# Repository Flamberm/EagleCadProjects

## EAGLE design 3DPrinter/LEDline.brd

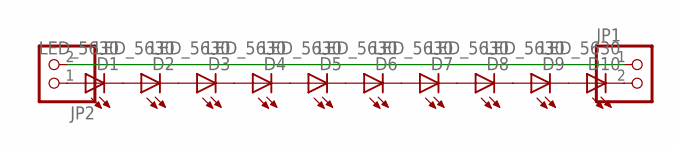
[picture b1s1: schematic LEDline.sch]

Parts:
D1, D2, D3, D4, D5, D6, D7, D8, D9, D10: LED_5630; LED5730
JP1, JP2: PINHD-1X2/90; 1X02/90

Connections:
unnamed: D1.C, D2.A, D2.A1 (A)
unnamed: D2.C, D3.A, D3.A1 (A)
unnamed: D3.C, D4.A, D4.A1 (A)
unnamed: D4.C, D5.A, D5.A1 (A)
unnamed: D5.C, D6.A, D6.A1 (A)
unnamed: D6.C, D7.A, D7.A1 (A)
unnamed: D7.C, D8.A, D8.A1 (A)
unnamed: D8.C, D9.A, D9.A1 (A)
unnamed: D9.C, D10.A, D10.A1 (A)
unnamed: D10.C, JP1.2
unnamed: D1.A, D1.A1 (A), JP2.1
unnamed: JP1.1, JP2.2

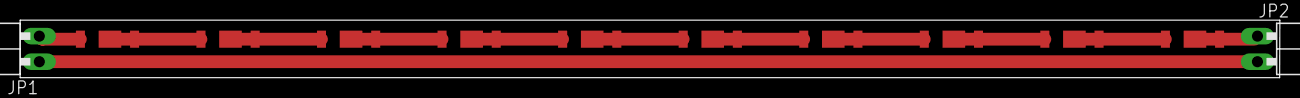
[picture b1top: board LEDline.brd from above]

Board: 2 copper layers, 125.1 x 5.7 mm, 12 parts (0 on the bottom side), 12 nets.

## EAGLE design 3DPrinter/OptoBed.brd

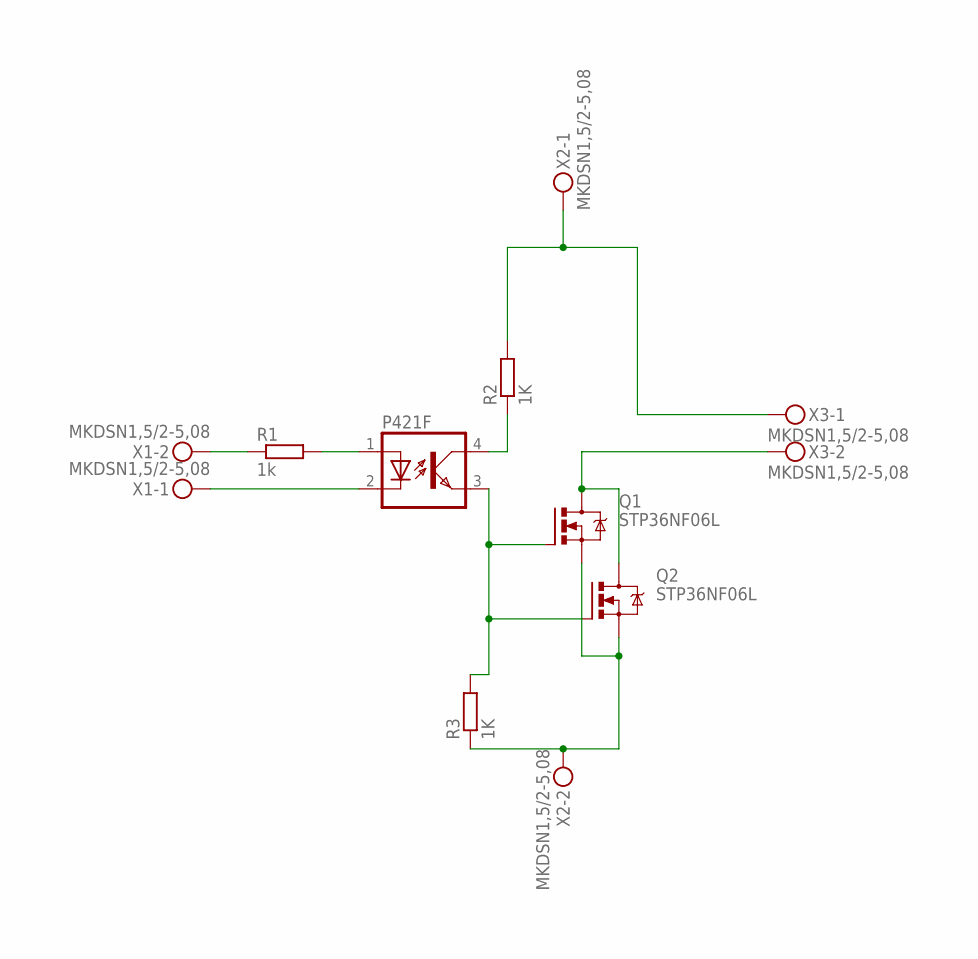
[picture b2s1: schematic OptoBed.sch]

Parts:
P421F: OPTOTRANSPC817; DIL04
Q1, Q2: STP36NF06L; TO220BV
R1: 1k; R0805
R2, R3: 1K; R0805
X1, X2, X3: MKDSN1,5/2-5,08

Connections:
unnamed: R1.1, X1.2
unnamed: P421F.1 (A), R1.2
unnamed: P421F.2 (C), X1.1
unnamed: P421F.3 (EMIT), Q1.G, Q2.G, R3.2
unnamed: Q1.S, Q2.S, R3.1, X2.2
unnamed: Q1.D, Q2.D, X3.2
unnamed: P421F.4 (COL), R2.1
unnamed: R2.2, X2.1, X3.1

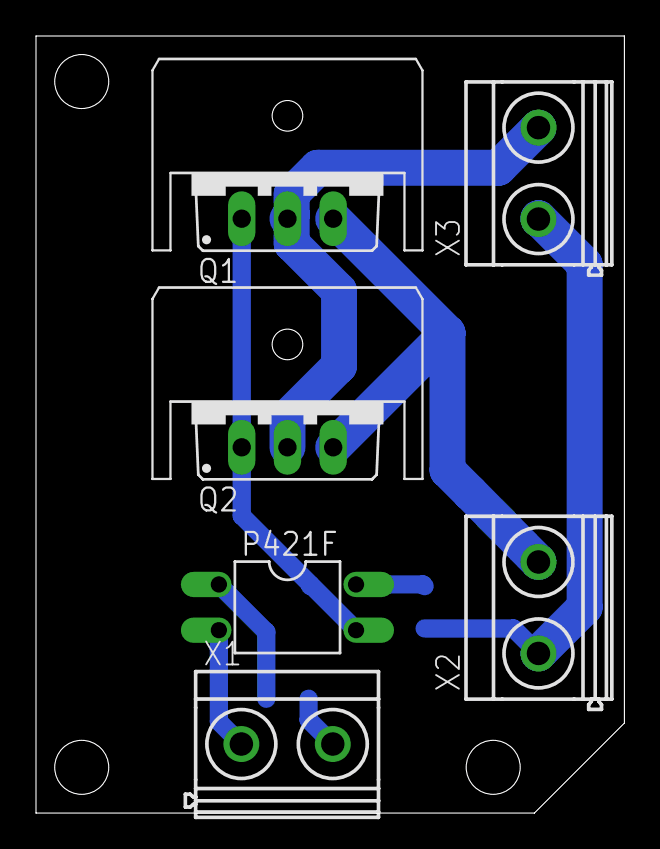
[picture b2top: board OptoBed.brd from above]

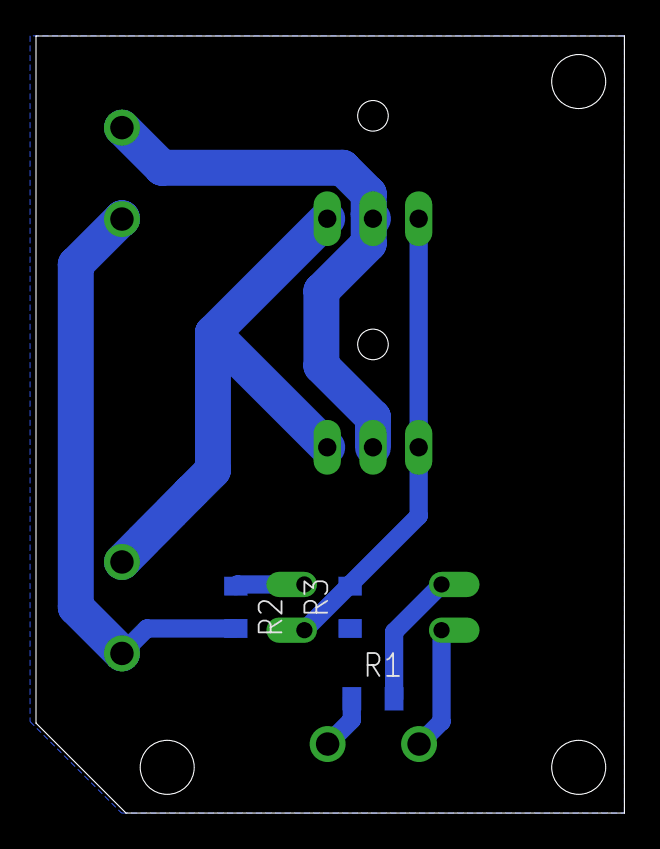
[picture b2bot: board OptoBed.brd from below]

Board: 2 copper layers, 32.7 x 43.2 mm, 11 parts (3 on the bottom side), 8 nets.

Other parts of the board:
U$1, U$2: SK95-3M3_HOLE

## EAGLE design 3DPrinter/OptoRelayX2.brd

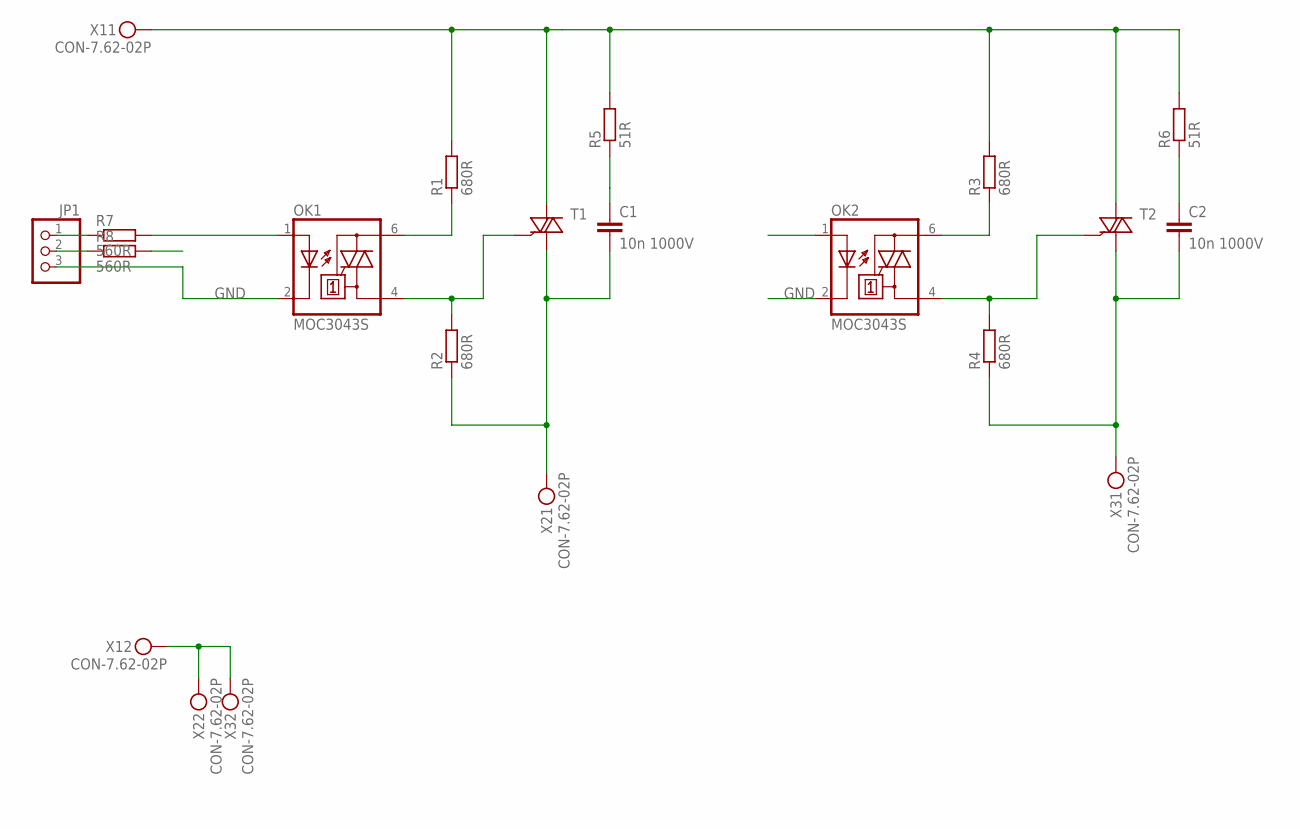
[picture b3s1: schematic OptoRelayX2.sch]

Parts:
C1, C2: 10n 1000V; C050-024X044
JP1: PINHD-1X3; 1X03
OK1, OK2: MOC3043S; DIL6-SMD
R1, R2, R3, R4: 680R; MF-05
R5, R6: 51R; MF-2
R7, R8: 560R; R0805
T1, T2: TRIAC; DPAK
X1, X2, X3: CON-7.62-02P; KF25C-7.62-02P-13

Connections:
GND: JP1.3, OK1.2 (C), OK2.2 (C)
unnamed: X1.P$2, X2.P$2, X3.P$2
unnamed: R1.2, R3.2, R5.2, R6.2, T1.D (A2), T2.D (A2), X1.P$1
unnamed: C1.1, R5.1
unnamed: OK1.6 (A2), R1.1
unnamed: OK2.6 (A2), R3.1
unnamed: OK2.4 (A1), R4.2, T2.S (G)
unnamed: OK1.4 (A1), R2.2, T1.S (G)
unnamed: C1.2, R2.1, T1.G (A1), X2.P$1
unnamed: C2.2, R4.1, T2.G (A1), X3.P$1
unnamed: C2.1, R6.1
unnamed: JP1.1, R7.1
unnamed: JP1.2, R8.1
unnamed: OK1.1 (A), R7.2
unnamed: OK2.1 (A), R8.2

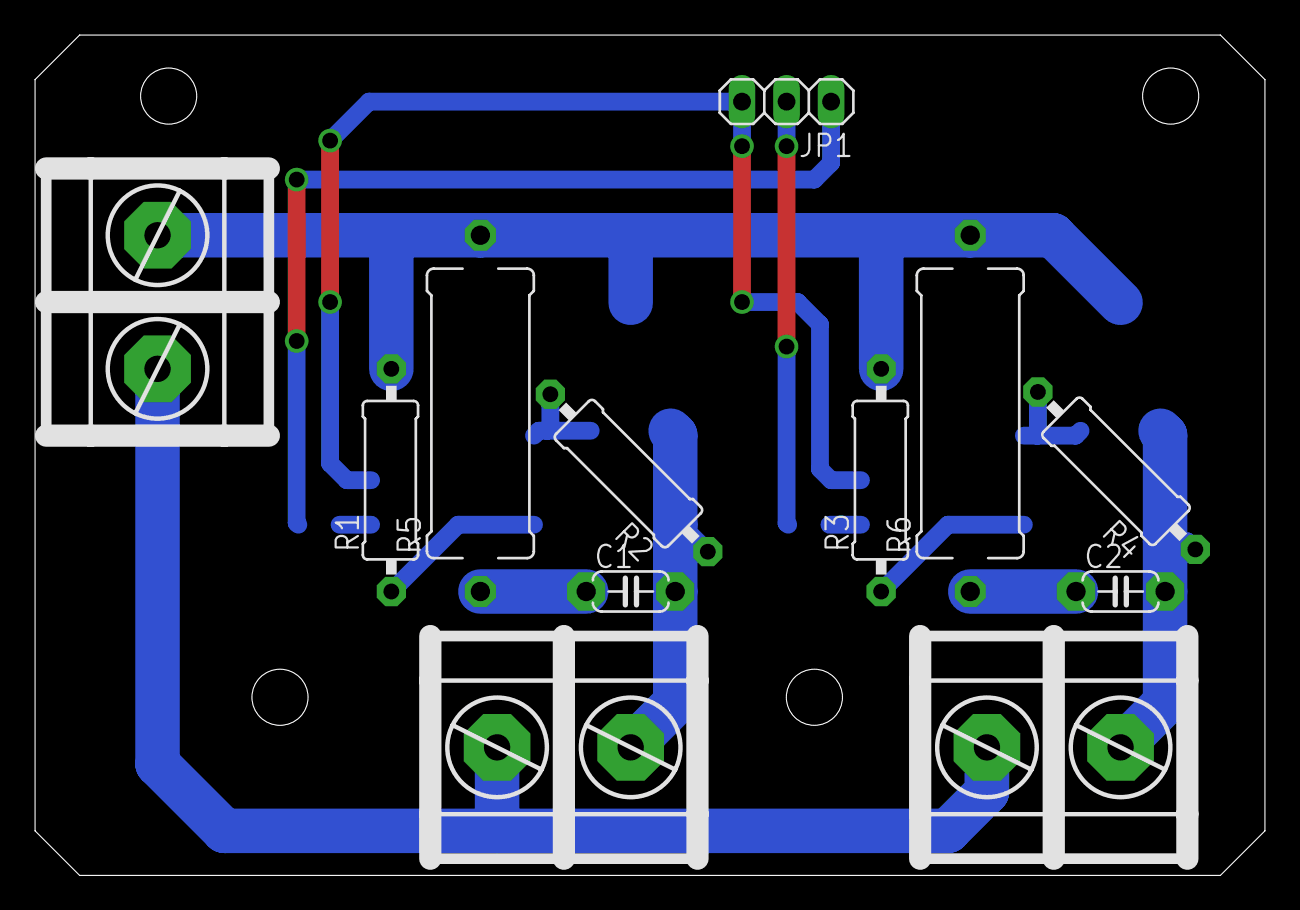
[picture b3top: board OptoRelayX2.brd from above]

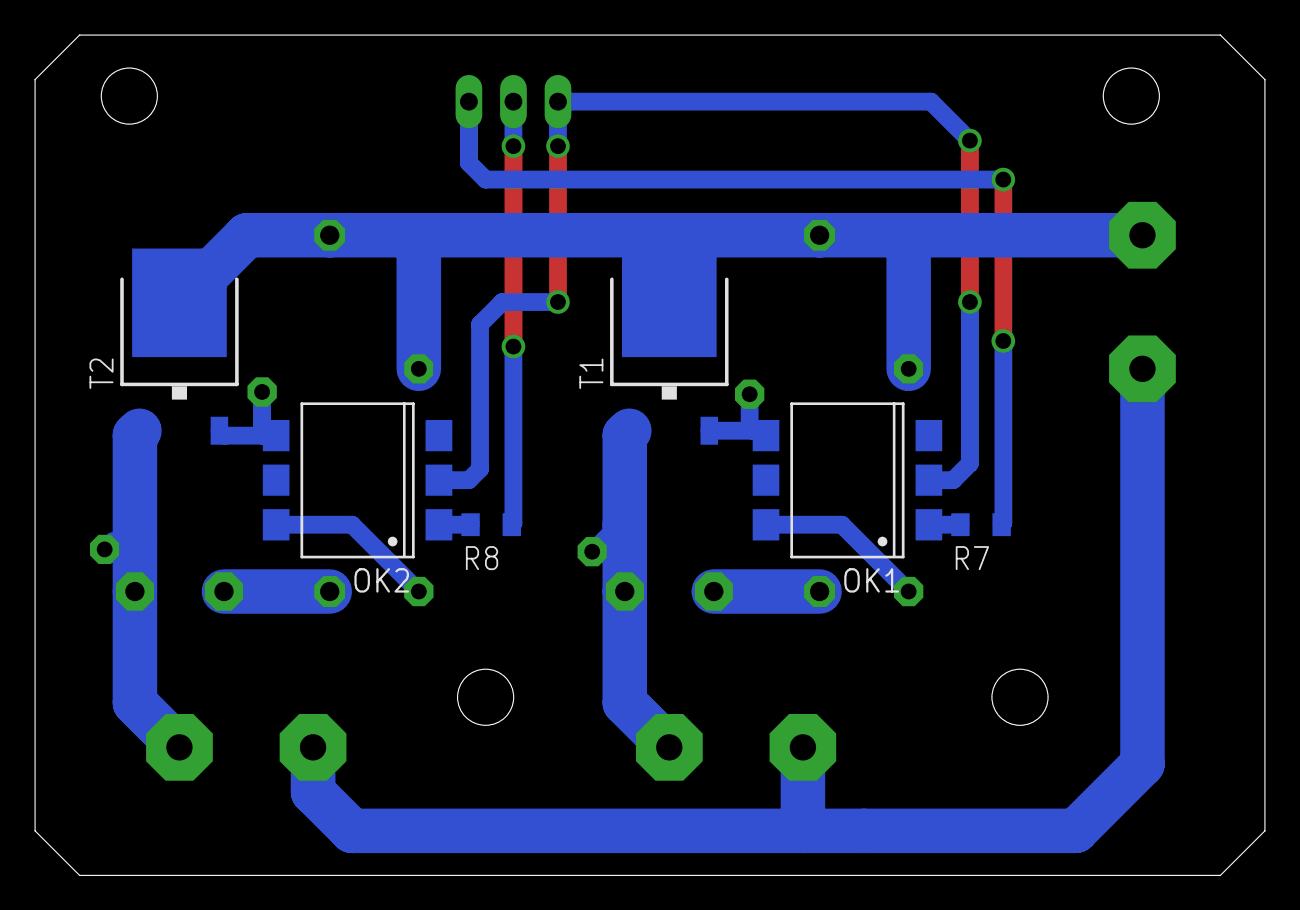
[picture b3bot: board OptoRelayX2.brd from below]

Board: 2 copper layers, 70.1 x 47.9 mm, 18 parts (6 on the bottom side), 15 nets.

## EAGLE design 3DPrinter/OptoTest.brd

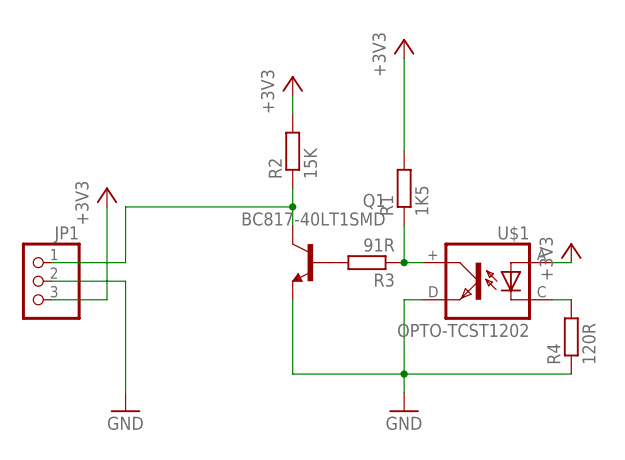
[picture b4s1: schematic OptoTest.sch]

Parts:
JP1: PINHD-1X3/90; 1X03/90
Q1: BC817-40LT1SMD; SOT23-BEC
R1: 1K5; R0805
R2: 15K; R0805
R3: 91R; R0805
R4: 120R; R0805
U$1: OPTO-TCST1202; TCST1202

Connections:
+3V3: JP1.3, R1.2, R2.2, U$1.A
GND: JP1.2, Q1.E, R4.1, U$1.D (EMIT)
unnamed: R1.1, R3.1, U$1.+ (COL)
unnamed: Q1.B, R3.2
unnamed: JP1.1, Q1.C, R2.1
unnamed: R4.2, U$1.C

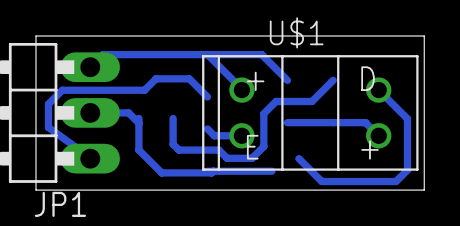
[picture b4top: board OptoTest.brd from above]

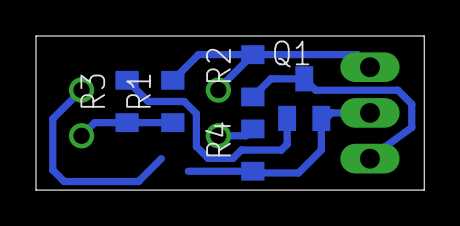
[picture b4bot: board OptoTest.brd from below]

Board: 2 copper layers, 21.6 x 8.6 mm, 7 parts (5 on the bottom side), 6 nets.

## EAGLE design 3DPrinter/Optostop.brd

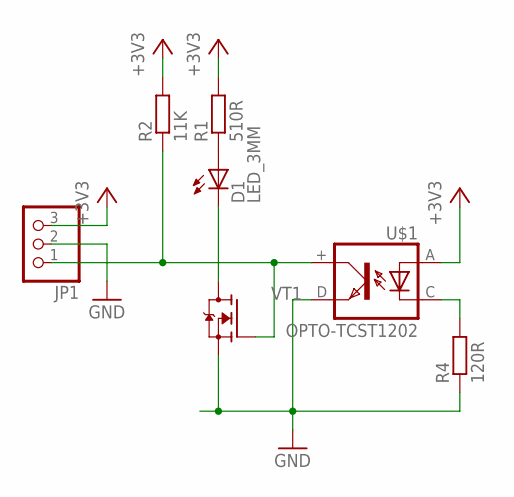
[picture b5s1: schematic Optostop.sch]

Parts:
D1: LED_3MM; LED3MM
JP1: PINHD-1X3/90; 1X03/90
R1: 510R; R0805
R2: 11K; R0805
R4: 120R; R0805
U$1: OPTO-TCST1202; TCST1202
VT1: FET-NSOT-23; SOT23

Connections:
+3V3: JP1.3, R1.2, R2.2, U$1.A
GND: JP1.2, R4.1, U$1.D (EMIT), VT1.2 (S)
unnamed: D1.A, R1.1
unnamed: JP1.1, R2.1, U$1.+ (COL), VT1.1 (G)
unnamed: D1.K (C), VT1.3 (D)
unnamed: R4.2, U$1.C

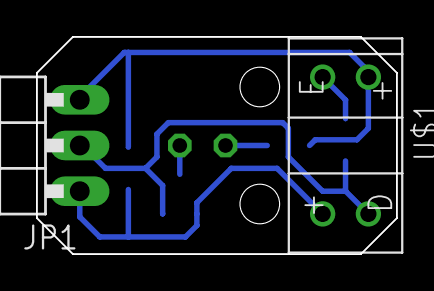
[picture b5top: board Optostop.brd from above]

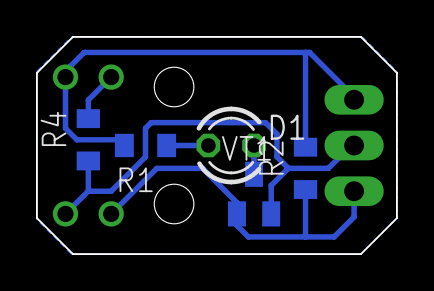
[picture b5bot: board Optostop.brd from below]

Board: 2 copper layers, 20.0 x 12.1 mm, 7 parts (5 on the bottom side), 6 nets.

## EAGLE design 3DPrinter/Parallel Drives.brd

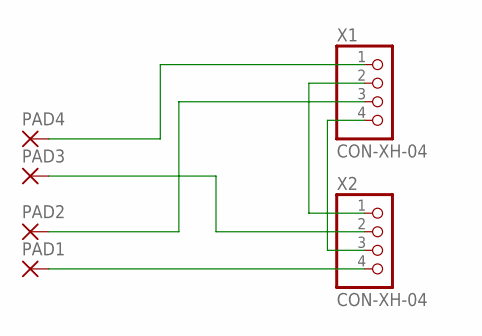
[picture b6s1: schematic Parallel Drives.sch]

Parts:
PAD1, PAD2, PAD3, PAD4: SMD2; SMD1,27-2,54
X1, X2: CON-XH-04; XH-04

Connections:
unnamed: PAD1.1, X2.4
unnamed: X1.4, X2.3
unnamed: PAD2.1, X1.3
unnamed: PAD3.1, X2.2
unnamed: X1.2, X2.1
unnamed: PAD4.1, X1.1

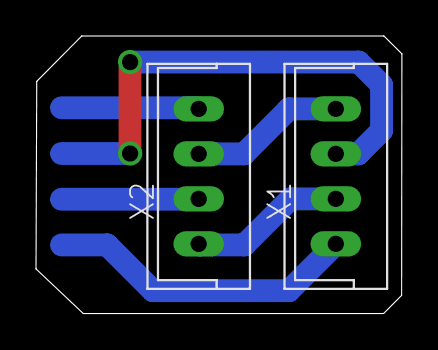
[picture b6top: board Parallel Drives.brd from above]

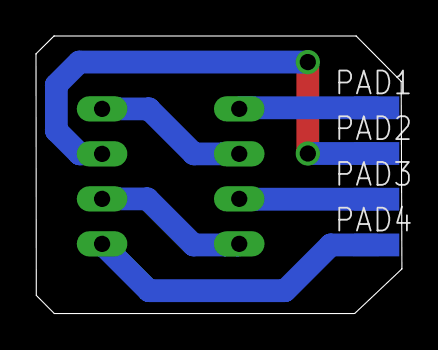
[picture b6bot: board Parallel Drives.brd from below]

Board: 2 copper layers, 20.3 x 15.4 mm, 6 parts (4 on the bottom side), 6 nets.

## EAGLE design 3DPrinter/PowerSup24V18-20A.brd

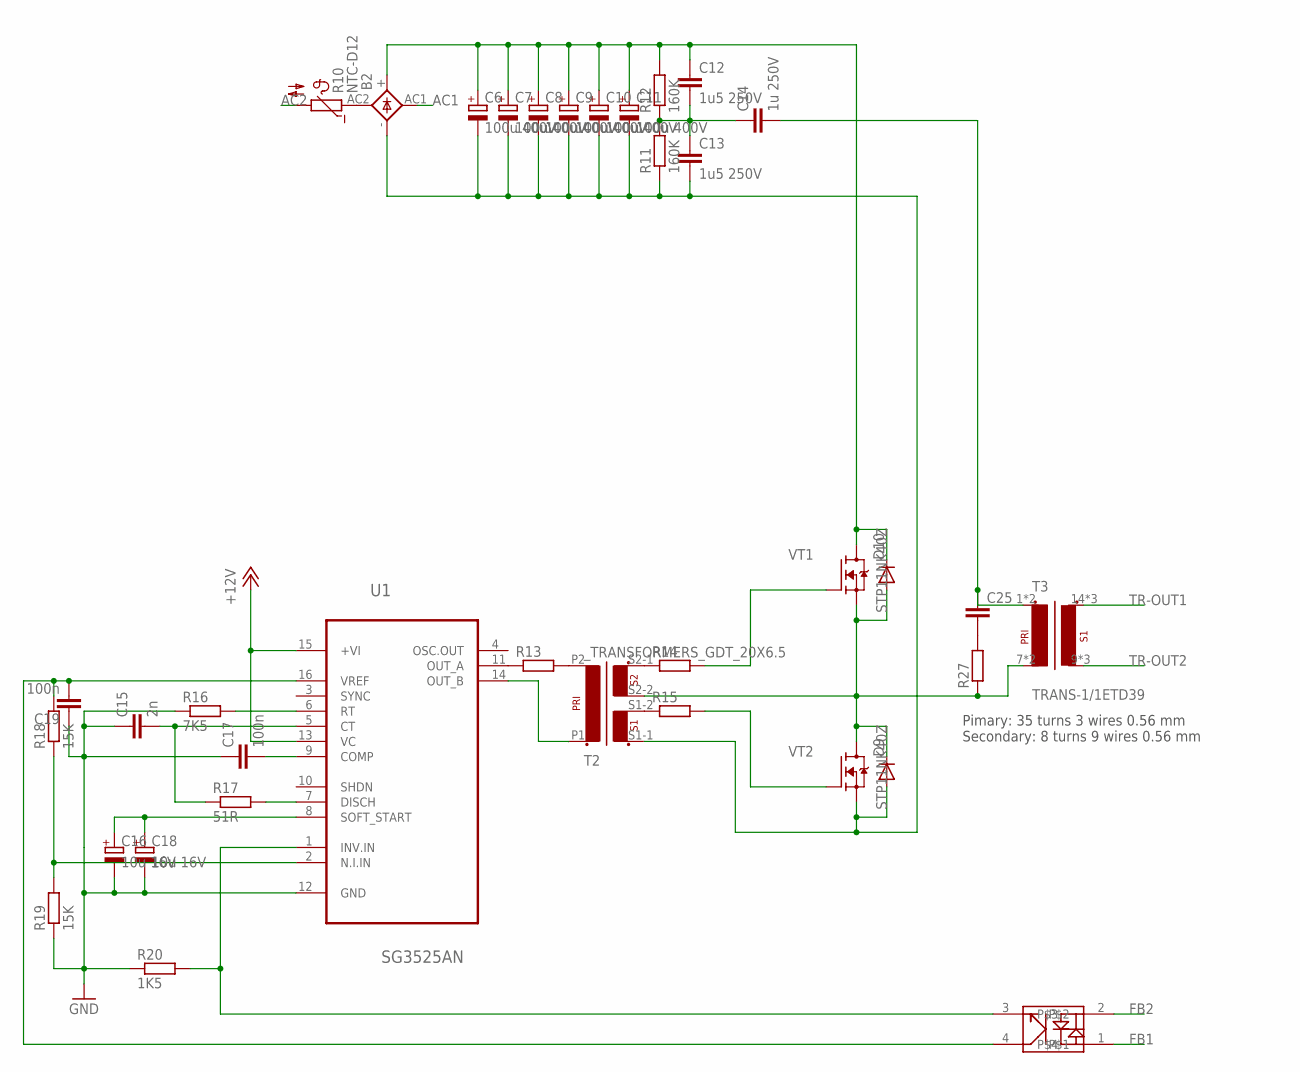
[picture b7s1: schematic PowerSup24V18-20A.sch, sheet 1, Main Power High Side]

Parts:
B2: RECTIFIERKBL; KBL
C6, C7, C8, C9, C10, C11: 100u 400V; E7,5-18
C12, C13: 1u5 250V; C225-074X268
C14: 1u 250V; C225-074X268
C15: 2n; C0805
C16, C18: 10u 16V; CT3528
C17, C19: 100n; C0805
C25: CAP_C50-024X044; C050-024X044
D9, D10: DIODE_ES1J; DO214AC
R10: NTC-D12
R11, R12: 160K; MF-0125
R13, R14, R15: R_1206; R1206
R16: 7K5; R0805
R17: 51R; R0805
R18, R19: 15K; R0805
R20: 1K5; R0805
R27: R_MF-2; MF-2
T2: _TRANSFORMERS_GDT_20X6.5
T3: TRANS-1/1ETD39; ETD39
U1: SG3525AN; DIP254P762X510-16
U$1: OPTO-EL3H4(TA)-VG; SSOP4
VT1, VT2: STP11NK40Z; TO-220V

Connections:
+12V: U1.13 (VC), U1.15 (+VI); also elsewhere on the board
AC1: B2.AC1 (AC2); also elsewhere on the board
AC2: R10.2; also elsewhere on the board
FB1: U$1.1; also elsewhere on the board
FB2: U$1.2; also elsewhere on the board
GND: C15.1, C16.-, C17.1, C18.-, C19.1, R16.1, R19.1, R20.1, U1.12 (GND); also elsewhere on the board
unnamed: B2.AC2 (AC1), R10.1
unnamed: C12.2, C13.1, C14.1, R11.2, R12.1
unnamed: B2.+, C6.+, C7.+, C8.+, C9.+, C10.+, C11.+, C12.1, D10.C, R12.2, VT1.2 (D)
unnamed: B2.-, C6.-, C7.-, C8.-, C9.-, C10.-, C11.-, C13.2, D9.A, R11.1, T2.S1-1, VT2.3 (S)
unnamed: R13.1, U1.11 (OUT_A)
unnamed: T2.P1 (P1-1), U1.14 (OUT_B)
unnamed: R13.2, T2.P2 (P1-2)
unnamed: R14.1, T2.S2-1
unnamed: R15.1, T2.S1-2
unnamed: R14.2, VT1.1 (G)
unnamed: R15.2, VT2.1 (G)
unnamed: D9.C, D10.A, R27.1, T2.S2-2, T3.7 (P1-2), T3.8 (P1-2), VT1.3 (S), VT2.2 (D)
unnamed: C14.2, C25.1, T3.1 (P1-1), T3.2 (P1-1)
unnamed: R16.2, U1.6 (RT)
unnamed: C15.2, R17.1, U1.5 (CT)
unnamed: C19.2, R18.2, U1.16 (VREF), U$1.4
unnamed: R17.2, U1.7 (DISCH)
unnamed: C16.+, C18.+, U1.8 (SOFT_START)
unnamed: R18.1, R19.2, U1.2 (N.I.IN)
unnamed: C17.2, U1.9 (COMP)
unnamed: R20.2, U1.1 (INV.IN), U$1.3
unnamed: C25.2, R27.2
TR-OUT1: T3.9 (S1-2), T3.10 (S1-2), T3.11 (S1-2); also elsewhere on the board
TR-OUT2: T3.14 (S1-1), T3.15 (S1-1), T3.16 (S1-1); also elsewhere on the board

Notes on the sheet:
Pimary: 35 turns 3 wires 0.56 mm Secondary: 8 turns 9 wires 0.56 mm

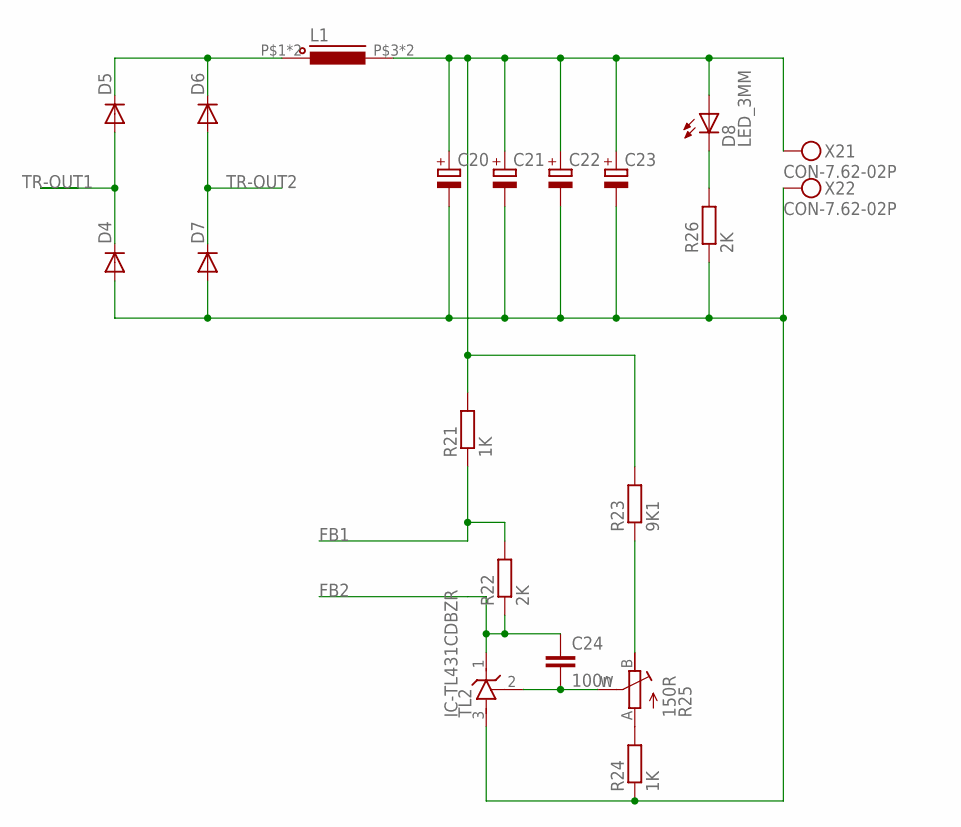
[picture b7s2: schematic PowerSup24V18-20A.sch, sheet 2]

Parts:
C20, C21, C22, C23: CPOL-EUE5-13; E5-13
C24: 100n; C0805
D4, D5, D6, D7: DIODE_TO-220-2; TO220ACS
D8: LED_3MM; LED3MM
L1: INDUCTORD26.7; D26.9/14.7/11.2
R21, R24: 1K; R0805
R22, R26: 2K; R0805
R23: 9K1; R0805
R25: 150R; RJ9W
TL2: IC-TL431CDBZR; SOT23
X2: CON-7.62-02P; KF25C-7.62-02P-13

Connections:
FB1: R21.1, R22.2; also elsewhere on the board
FB2: C24.1, R22.1, TL2.1 (C); also elsewhere on the board
unnamed: D5.C, D6.C, L1.P$1 (1), L1.P$2 (1)
unnamed: C20.-, C21.-, C22.-, C23.-, D4.A, D7.A, R24.1, R26.1, TL2.3 (A), X2.P$2
unnamed: C20.+, C21.+, C22.+, C23.+, D8.A, L1.P$3 (2), L1.P$4 (2), R21.2, R23.2, X2.P$1
unnamed: R24.2, R25.A
unnamed: R23.1, R25.B (E)
unnamed: C24.2, R25.W (S), TL2.2 (R)
unnamed: D8.K (C), R26.2
TR-OUT1: D4.C, D5.A; also elsewhere on the board
TR-OUT2: D6.A, D7.C; also elsewhere on the board

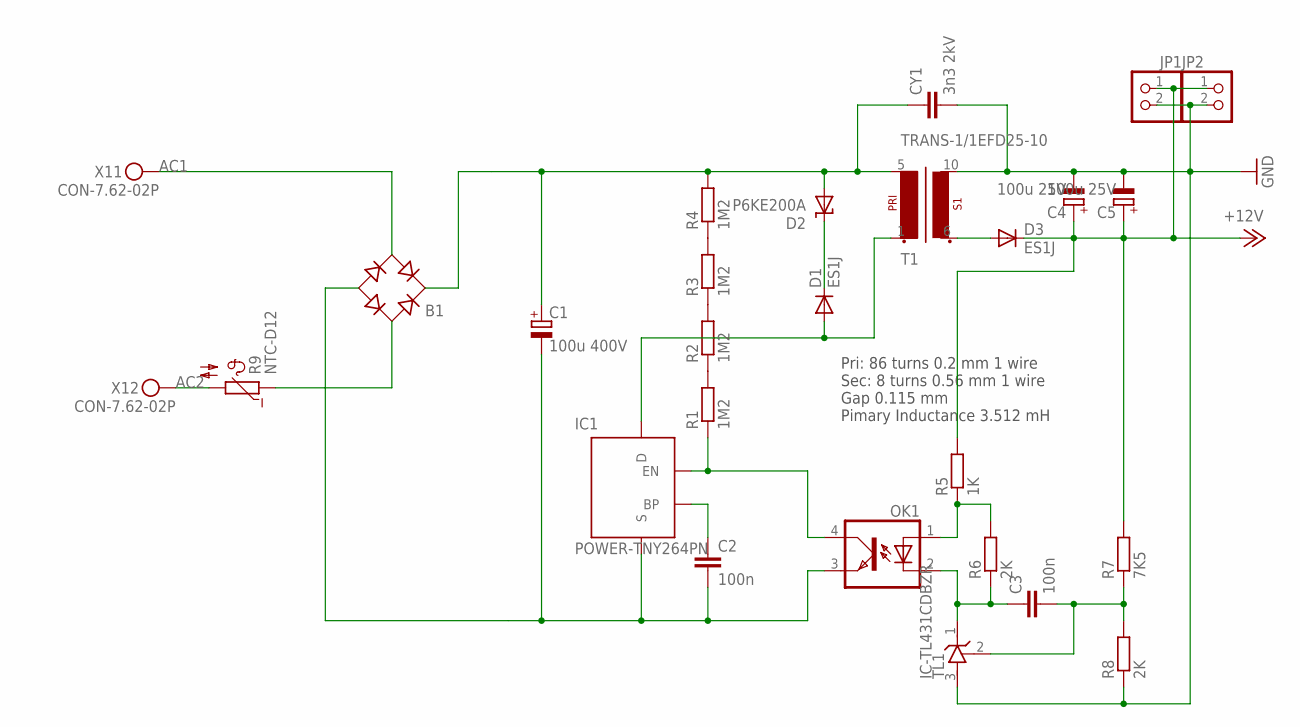
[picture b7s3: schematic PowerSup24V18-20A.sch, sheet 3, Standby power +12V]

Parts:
B1: RB1A
C1: 100u 400V; E7,5-18
C2, C3: 100n; C0805
C4, C5: 100u 25V; E2,5-7
CY1: 3n3 2kV; YC7B5
D1, D3: ES1J; DO214AC
D2: P6KE200A; DO15-12
IC1: POWER-TNY264PN; DIP-8B
JP1, JP2: PINHD-1X2; 1X02
OK1: OPTOTRANSPC817; DIL04
R1, R2, R3, R4: 1M2; R0805
R5: 1K; R0805
R6, R8: 2K; R0805
R7: 7K5; R0805
R9: NTC-D12
T1: TRANS-1/1EFD25-10; EFD25_10PIN
TL1: IC-TL431CDBZR; SOT23
X1: CON-7.62-02P; KF25C-7.62-02P-13

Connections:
+12V: C4.+, C5.+, D3.C, JP1.1, JP2.1, R5.2, R7.2; also elsewhere on the board
AC1: B1.AC2, X1.P$1; also elsewhere on the board
AC2: R9.2, X1.P$2; also elsewhere on the board
GND: C4.-, C5.-, CY1.2, JP1.2, JP2.2, R8.1, T1.10 (S1-2), TL1.3 (A); also elsewhere on the board
unnamed: B1.AC1, R9.1
unnamed: B1.+, C1.+, CY1.1, D2.A, R4.2, T1.5 (P1-2)
unnamed: B1.-, C1.-, C2.2, IC1.2 (S), IC1.3 (S), IC1.7 (S), IC1.8 (S), OK1.3 (EMIT)
unnamed: R1.2, R2.1
unnamed: R2.2, R3.1
unnamed: R3.2, R4.1
unnamed: IC1.4 (EN), OK1.4 (COL), R1.1
unnamed: D1.A, IC1.5 (D), T1.1 (P1-1)
unnamed: D1.C, D2.C
unnamed: C2.1, IC1.1 (BP)
unnamed: C3.1, OK1.2 (C), R6.1, TL1.1 (C)
unnamed: OK1.1 (A), R5.1, R6.2
unnamed: C3.2, R7.1, R8.2, TL1.2 (R)
unnamed: D3.A, T1.6 (S1-1)

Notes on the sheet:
Pri: 86 turns 0.2 mm 1 wire Sec: 8 turns 0.56 mm 1 wire Gap 0.115 mm Pimary Inductance 3.512 mH
